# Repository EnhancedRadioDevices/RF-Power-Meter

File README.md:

Enhanced Radio Devices - RF Power Meter
=======

The ERD RF Power Meter is designed as an affordable RF Power Meter for use in cases where the precision of expensive professional equipment is not required.

The device is available to the host system as a USB serial device, which when accessed automatically prints the measured RF level.

This repository contains the source code to be compiled with AVR-GCC, and uploaded to the device via ATMEL's FLIP programmer or the dfu-programmer utility.

## Drivers
The Power Meter board is automatically recognized as a USB serial device under OSX and Linux, however, windows requires a driver to associate the device with the built in USB serial device drivers.

When first attaching the device to a windows based host, windows will attempt to find a driver and fail. You may then specify a driver. This is provided in ERD_RF_Power_Meter.inf.

Once you have installed the driver, the Power Meter will register as a COM port device under windows, and you may access it with any serial/terminal application of your preference.

### Windows Users
During the driver installation process on Windows 8 operating systems and above you may encounter *"The third-party INF does not contain digital signature information"* preventing the installation of the included driver.  The steps below outline the process for disabling driver signature enforcement on Windows 8/8.1 systems.

**NOTE:** If your system uses BitLocker Drive Encryption, you will need your encryption key to gain access to advanced settings to disable driver signature enforcement.

Windows 8 - Navigate to PC settings > General and look for the *Advanced startup* dialog.  Click the **Restart now** button to access the advanced startup settings.  Your system will now reboot.

Windows 8.1 - Navigate to PC settings > Update and Recovery > Recovery and look for the *Advanced startup* dialog.  Click the **Restart now** button to access the advanced startup settings.  Your system will now reboot.

After rebooting select Troubleshoot > Advanced options > Startup Settings, click the **Restart** button, your machine will reboot a second time.

After rebooting a second time you should be presented with the Windows Startup Settings dialog, choose *Disable driver signature enforcement* by pressing number `7` on your keyboard.  Your machine will reboot automatically.

Once rebooted, you should now be able to install the drviers as outlined above.  Once the appropriate driver is selected you will see a Windows Security dialog warning against the installation of the unsigned driver.  Click **Install this driver software anyway** to complete the driver installation.

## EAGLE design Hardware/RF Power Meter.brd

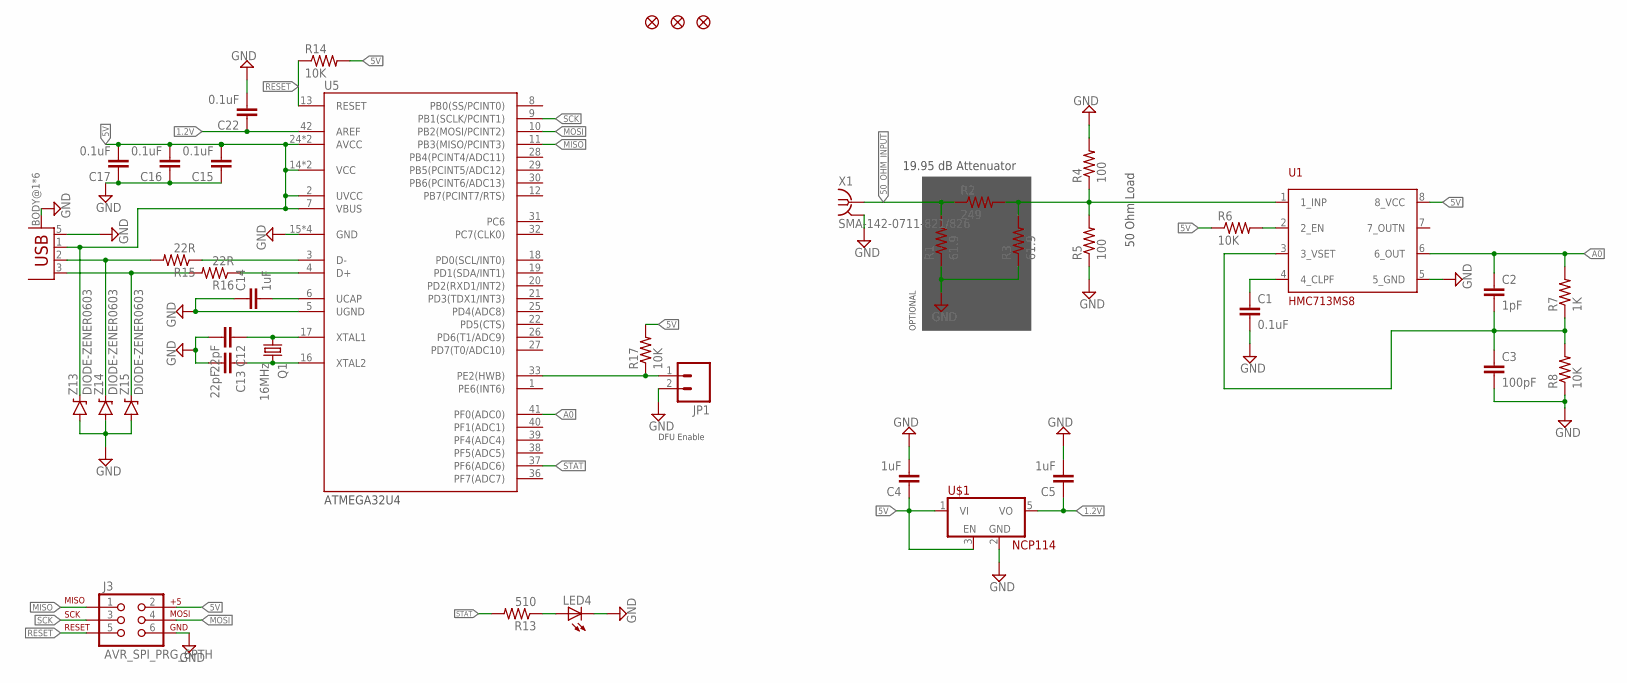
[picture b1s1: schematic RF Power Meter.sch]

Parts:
C1, C15, C16, C17, C22: 0.1uF; 0603-CAP
C2: 1pF; 0603-CAP
C3: 100pF; 0603-CAP
C4, C5, C14: 1uF; 0603-CAP
C12, C13: 22pF; 0603-CAP
J3: AVR_SPI_PRG_6PTH; 2X3
JP1: M02PTH3; 1X02_LONGPADS
JP2, JP3, JP4: FIDUCIAL1X2; FIDUCIAL-1X2
LED4: LED0603; LED-0603
Q1: 16MHz; CRYSTAL_3.2X2.5
R1, R3: 61.9; 1206
R2: 249; 1206
R4, R5: 100; 1206
R6, R8, R14, R17: 10K; 0603-RES
R7: 1K; 0603-RES
R13: 510; 0603-RES
R15, R16: 22R; 0603-RES
U1: HMC713MS8; MSOP-8
U5: ATMEGA32U4; TQFP-44
U$1: NCP114; SOT-23-5
X1: SMA-142-0711-821/826; J502-ND-142-0711-821/826
X3: USB-MICROB; USB-MICROB-10118192
Z13, Z14, Z15: DIODE-ZENER0603; 0603-DIODE

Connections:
1.2V: C5.1, C22.1, U5.42 (AREF), U$1.5 (VO)
5V: C4.1, C15.2, C16.2, C17.2, J3.2, R6.1, R14.2, R17.2, U1.8 (8_VCC), U5.2 (UVCC), U5.7 (VBUS), U5.14 (VCC), U5.24 (AVCC), U5.34 (VCC), U5.44 (AVCC), U$1.1 (VI), U$1.3 (EN), X3.1 (VBUS), Z13.C
50_OHM_INPUT: R1.2, R2.1, X1.1
A0: C2.1, R7.2, U1.6 (6_OUT), U5.41 (PF0(ADC0))
GND: C1.2, C3.2, C4.2, C5.2, C12.2, C13.2, C14.1, C15.1, C16.1, C17.1, C22.2, J3.6, JP1.2, LED4.C, R1.1, R3.1, R4.2, R5.1, R8.1, U1.5 (5_GND), U5.5 (UGND), U5.15 (GND), U5.23 (GND), U5.35 (GND), U5.43 (GND), U$1.2 (GND), X1.G@1 (2), X1.G@2 (2), X1.G@3 (2), X1.G@4 (2), X3.5 (GND), X3.BODY@1 (BODY), X3.BODY@2 (BODY), X3.BODY@3 (BODY), X3.BODY@4 (BODY), X3.BODY@5 (BODY), X3.BODY@6 (BODY), Z13.A, Z14.A, Z15.A
MISO: J3.1, U5.11 (PB3(MISO/PCINT3))
MOSI: J3.4, U5.10 (PB2(MOSI/PCINT2))
unnamed: R2.2, R3.2, R4.1, R5.2, U1.1 (1_INP)
unnamed: R6.2, U1.2 (2_EN)
unnamed: C1.1, U1.4 (4_CLPF)
unnamed: C2.2, C3.1, R7.1, R8.2, U1.3 (3_VSET)
unnamed: LED4.A, R13.1
unnamed: C12.1, Q1.P$1 (1), U5.17 (XTAL1)
unnamed: C13.1, Q1.P$3 (2), U5.16 (XTAL2)
unnamed: R15.2, X3.2 (D-), Z14.C
unnamed: C14.2, U5.6 (UCAP)
unnamed: R16.2, X3.3 (D+), Z15.C
unnamed: R16.1, U5.4 (D+)
unnamed: R15.1, U5.3 (D-)
unnamed: JP1.1, R17.1, U5.33 (PE2(HWB))
RESET: J3.5, R14.1, U5.13 (RESET)
SCK: J3.3, U5.9 (PB1(SCLK/PCINT1))
STAT: R13.2, U5.37 (PF6(ADC6))

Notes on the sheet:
OPTIONAL
19.95 dB Attenuator
50 Ohm Load
DFU Enable

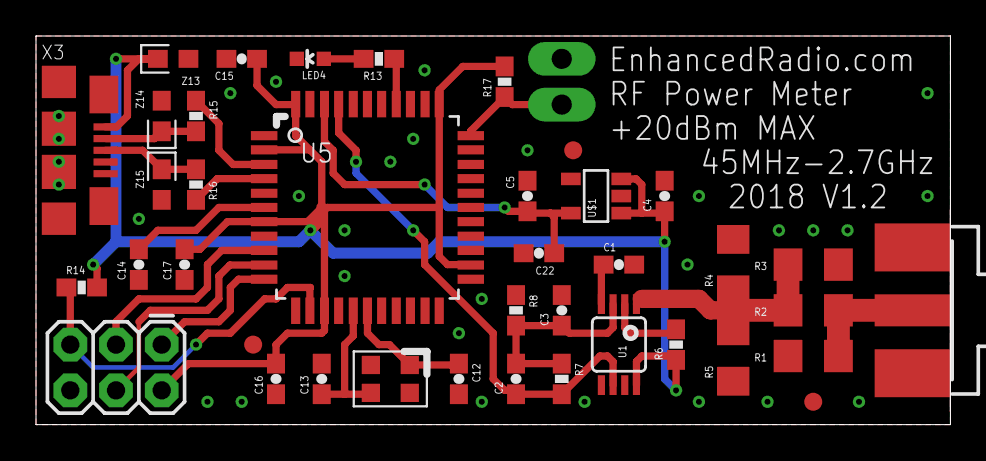
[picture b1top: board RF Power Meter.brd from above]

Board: 2 copper layers, 50.8 x 21.6 mm, 40 parts (0 on the bottom side), 23 nets.

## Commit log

2017-11-09 Initial commit. Basic functioning.
2017-11-09 Cleaned up some LUFA examples that aren't needed.
2018-01-09 Changed organization of the repo. Updated USB VID/PID. Added RF Freq Range to silkscreen. Added board schematic and layout files.
2018-03-22 Added EEPROM calibration tables based on frequency. Added command to set the current working frequency and load appropriate calibration data. Changed LED function to blink regularly with samples bein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
2018-03-22 Added OUTPUTRAW function to allow printing raw voltage readings rather than the calculated dBm values. Useful in calibration.
2018-03-23 Replaced placeholder calibration values. Added function to automatically init EEPROM with default calibration values if empty. Ready for new release.

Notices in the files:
parts and their libraries:
SparkFun: Licensing: CC v3.0 Share-Alike You are welcome to use this library for commercial purposes.
